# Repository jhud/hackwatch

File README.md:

# hackwatch
Want to run your Arduino code anywhere, any time? How about running a webserver from your wrist? This is a smartwatch running on the ESP32 + Arduino + 0.96' OLED (color or monochrome). Designed to run on cheap boards that have inbuilt LiPo battery circuitry and an OLED screen. It makes for quite a chunky watch, but the "always on" glow looks very cool, and a 500mAH battery currently lasts 10+ hours without any optimisation. The whole prototype was built for $12.

Currently, the code uses your WiFi to sync with an NTP server, then show the time and date. I'll improve this project as I need features and find time.

The "flash" button on the GPIO0 of the development board is repurposed as a function button for the watch.

## Features
 - Flashlight, Stopwatch, Timer, Wifi Scan, UV Sensor with daily exposure graph
 - BLE connection with message notifications
 - Hardcoded calendar functionality, which will remind you when you need to catch buses, etc.
 - Screen off button, goes into sleep mode
 - Switch between color or B&W display on the application level, via a high-level UI interface.

# Setup

## Installation

Install the following dependencies:
 - Time (from Arduino library manager)
 - ```git clone https://github.com/mgo-tec/ESP32_SSD1331``` (for the color SSD1331 display)
 - ```git clone https://github.com/Smartphone-Companions/ESP32NotificationsLib.git``` (for the Bluetooth LE notifications)

You need to create a file called "secrets.h" which has your WiFi SSID and password:

const char ssid[] = "my access point";  //  your network SSID (name)
const char pass[] = "MyPassword12345";       // your network password

If you have an SSD1306 monochrome display, remove the #define COLOR_SCREEN. If you have an SSD1331 color display, set that define. Make sure you have the correct pins set in layout.cpp.

### OSX Troubleshooting

 - On OSX Catalina you might have trouble getting the "TTGO ESP32 OLED" board recognised by Arduino. If so, try installing the driver for the USB chip. https://www.silabs.com/products/development-tools/software/usb-to-uart-bridge-vcp-drivers

# Fabrication
The SVG file can be printed out, and the pieces cut from 1.5mm rubber. For attaching rubber, here are the methods tried (1 star fail, 5 star excellent):
 - Stitching with nylon thread *****
 - Double-sided tape ***
 - Vulcanising rubber cement **
 - Electrical tape **
 - Hot glue *
 The best method was to stick pieces with double-sided tape, and then stitch any load-bearing joins.

# Major tasks yet to do:
- Big refactor of messy prototype code
- Reduce power consumption (i.e. deep sleep when not changing display)
- Piezo chime or vibrate

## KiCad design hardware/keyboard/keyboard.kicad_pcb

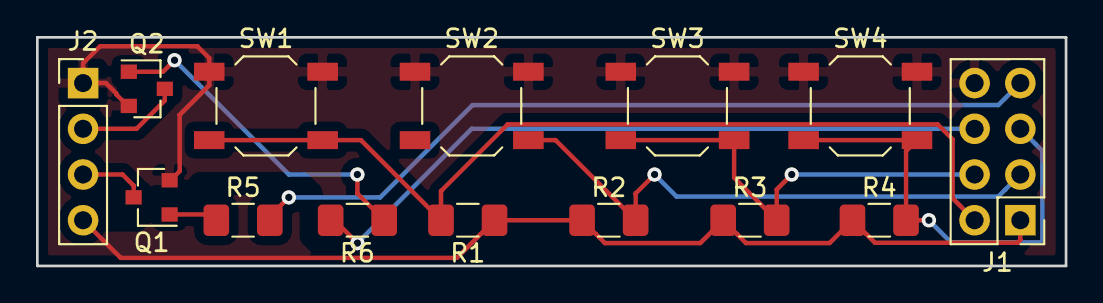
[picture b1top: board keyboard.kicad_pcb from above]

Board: 2 copper layers, 57.1 x 12.7 mm, 14 parts (0 on the bottom side), 12 nets.

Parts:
J1: Pin header; PinHeader_2x04_P2.54mm_Vertical
J2: Conn_01x04_Male; PinHeader_1x04_P2.54mm_Vertical
Q1, Q2: 2N7002; SOT-23
R1: 33K; R_1206_3216Metric_Pad1.42x1.75mm_HandSolder
R2, R3, R4, R5, R6: R; R_1206_3216Metric_Pad1.42x1.75mm_HandSolder
SW1, SW2, SW3, SW4: SW_Push; SW_SPST_TL3342

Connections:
GND: J1.8, J2.1, Q1.2, Q2.2, SW1.1, SW2.1, SW3.1, SW4.1
unnamed: J1.1, J2.4, R1.1, R2.1, R3.1, R4.1
unnamed: J1.2, R1.2, SW1.2
unnamed: J1.3, R2.2, SW2.2
unnamed: J1.4, R3.2, SW3.2
unnamed: J1.5, R4.2, SW4.2
unnamed: J1.6, R6.2
unnamed: J1.7, R5.2
unnamed: J2.2, Q2.3
unnamed: J2.3, Q1.3
unnamed: Q1.1, R5.1
unnamed: Q2.1, R6.1

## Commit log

2018-01-21 Changed license.
2018-01-31 Multi wifi connection, timeout for network failures, calendar functions.
2018-02-01 Added binary ticker for fun.
2018-02-02 Current consumption in standby is < 5mA
2018-02-20 Added stopwatch and button handling.
2018-02-20 Added basic menu and navigation.
2018-02-21 pic of new band
2018-02-23 Wifi scanner added.
2018-02-28 Refactored rendering, all font selection done automatically.
2018-03-06 Update LICENSE
2018-03-19 Abstracted away display code.
2018-03-23 Added support for SSD1331 color display
2018-04-01 Added uv sensor
2019-02-22 Added UV graphing
2019-02-27 Push notifications working.
2019-12-20 Uses BLENotifications library.
2019-12-20 Added ESP32NotificationsLib as a dependency
2020-05-01 Updated to work with latest ANCS library. Added code to hit an IoT HTTP server, so room lights can be toggled from the watch.
2025-02-01 Updated to latest libraries. Removed hardcoded access points + passwords.

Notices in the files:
hardware/keyboard/keyboard.kicad_pcb:
Hackwatch Buttonboard v1.0 (c)2019 James Hudson
